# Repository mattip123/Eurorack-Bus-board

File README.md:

# Eurorack Bus board
Bus board with 16 pin connectors
cc-by-sa-3.0
Status: Works fine.

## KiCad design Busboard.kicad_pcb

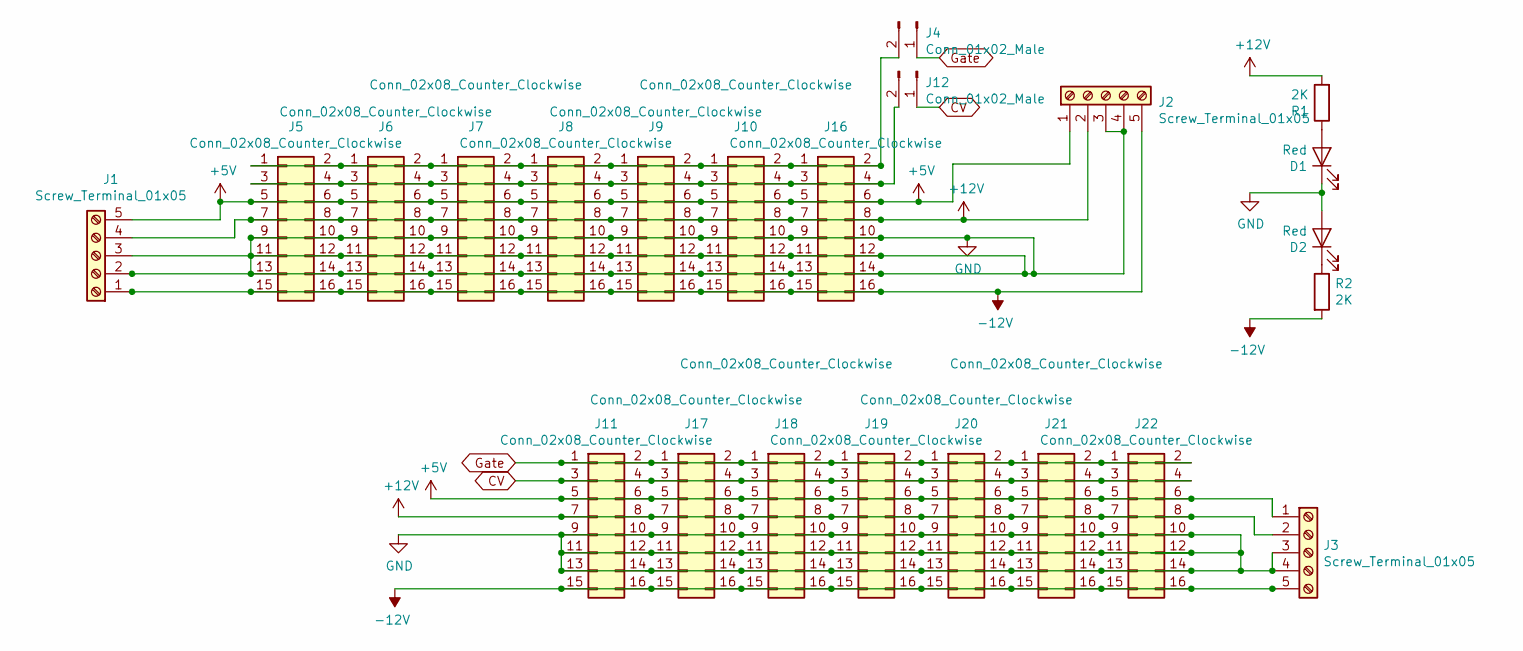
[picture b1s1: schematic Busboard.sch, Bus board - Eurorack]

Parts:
D1, D2: Red; LED_D3.0mm
J1, J2, J3: Screw_Terminal_01x05; TerminalBlock_RND_205-00048_1x05_P5.00mm_Horizontal
J4, J12: Conn_01x02_Male; PinHeader_1x02_P2.54mm_Vertical
J5, J6, J7, J8, J9, J10, J11, J16, J17, J18, J19, J20, J21, J22: Conn_02x08_Counter_Clockwise; IDC-Header_2x08_P2.54mm_Vertical
R1, R2: 2K; R_Axial_DIN0309_L9.0mm_D3.2mm_P12.70mm_Horizontal

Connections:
+5V: J1.5, J2.1, J3.1, J5.5, J5.6, J6.5, J6.6, J7.5, J7.6, J8.5, J8.6, J9.5, J9.6, J10.5, J10.6, J11.5, J11.6, J16.5, J16.6, J17.5, J17.6, J18.5, J18.6, J19.5, J19.6, J20.5, J20.6, J21.5, J21.6, J22.5, J22.6
+12V: J1.4, J2.2, J3.2, J5.7, J5.8, J6.7, J6.8, J7.7, J7.8, J8.7, J8.8, J9.7, J9.8, J10.7, J10.8, J11.7, J11.8, J16.7, J16.8, J17.7, J17.8, J18.7, J18.8, J19.7, J19.8, J20.7, J20.8, J21.7, J21.8, J22.7, J22.8, R1.2
-12V: J1.1, J2.5, J3.5, J5.15, J5.16, J6.15, J6.16, J7.15, J7.16, J8.15, J8.16, J9.15, J9.16, J10.15, J10.16, J11.15, J11.16, J16.15, J16.16, J17.15, J17.16, J18.15, J18.16, J19.15, J19.16, J20.15, J20.16, J21.15, J21.16, J22.15, J22.16, R2.2
CV: J11.3, J11.4, J12.1, J17.3, J17.4, J18.3, J18.4, J19.3, J19.4, J20.3, J20.4, J21.3, J21.4, J22.3, J22.4
GND: D1.1 (K), D2.2 (A), J1.2, J1.3, J2.3, J2.4, J3.3, J3.4, J5.9, J5.10, J5.11, J5.12, J5.13, J5.14, J6.9, J6.10, J6.11, J6.12, J6.13, J6.14, J7.9, J7.10, J7.11, J7.12, J7.13, J7.14, J8.9, J8.10, J8.11, J8.12, J8.13, J8.14, J9.9, J9.10, J9.11, J9.12, J9.13, J9.14, J10.9, J10.10, J10.11, J10.12, J10.13, J10.14, J11.9, J11.10, J11.11, J11.12, J11.13, J11.14, J16.9, J16.10, J16.11, J16.12, J16.13, J16.14, J17.9, J17.10, J17.11, J17.12, J17.13, J17.14, J18.9, J18.10, J18.11, J18.12, J18.13, J18.14, J19.9, J19.10, J19.11, J19.12, J19.13, J19.14, J20.9, J20.10, J20.11, J20.12, J20.13, J20.14, J21.9, J21.10, J21.11, J21.12, J21.13, J21.14, J22.9, J22.10, J22.11, J22.12, J22.13, J22.14
Gate: J4.1, J11.1, J11.2, J17.1, J17.2, J18.1, J18.2, J19.1, J19.2, J20.1, J20.2, J21.1, J21.2, J22.1, J22.2
unnamed: D1.2 (A), R1.1
unnamed: D2.1 (K), R2.1
unnamed: J4.2, J5.1, J5.2, J6.1, J6.2, J7.1, J7.2, J8.1, J8.2, J9.1, J9.2, J10.1, J10.2, J16.1, J16.2
unnamed: J5.3, J5.4, J6.3, J6.4, J7.3, J7.4, J8.3, J8.4, J9.3, J9.4, J10.3, J10.4, J12.2, J16.3, J16.4

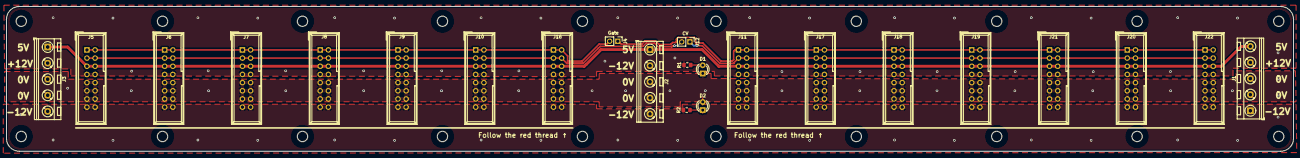
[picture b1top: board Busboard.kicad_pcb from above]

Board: 2 copper layers, 400.0 x 45.0 mm, 23 parts (0 on the bottom side), 10 nets.

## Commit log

2019-08-27 v02
    OK, I added 5V and gate and CV. No regulator or jumpers, though.
2019-08-29 v02
    Added jumpers for Gate and CV.
    Changed to screw terminals.
2020-01-09 Update README.md
    Works fine.
